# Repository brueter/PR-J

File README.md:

<p align="center">
    <picture>
        <source media="(prefers-color-scheme: dark)" srcset="./images/dark.svg" | width=300>
        <source media="(prefers-color-scheme: light)" srcset="./images/light.svg" | width=300>
        
    </picture>
</p>

## PR and what now?
PR&J is the second name of this project after realizing two things:
- I'd like to be able to put this on a resume.
- Realizing the main features are as follows:
    - Probing
    - Runout detection
    - & Jam detection
> This board also is sandwiched between the hotend and extruder, thus a PR&J.

> If you'd like to know the first name of the board scroll up a bit in the discord

## How does a load cell do all that?
The way this design is set to work is there will be a strain gauge between the extruder and hotend with a set of resistors on it.
When the board experiences even the slightest bit of strain, the value of these resistors changes slightly.
This change is amplified by the tried and true HX717 24 bit amplifier, allowing for over 16 million unique values.
This signal is then read by an on board ATTiny202, and then sent to a klipper MCU via I<sub>2</sub>C.

Though the first idea that comes to mind with load cells is probing (which is still the main feature of this project), the ability to detect this strain can also be used to interpret forces between the hotend and extruder in both positive and negative directions.
We're still workshopping ideas that could come from this one feature, but some we would like to consider are:
- Runout detection
- Jam detection
- Detecting skipped steps
- One-click pressure advance tuning
- One-click max flow rate calculation

Some "theoreticals" that will need extensive testing but may be possible:
- Spaghetti detection
- Crash detection
- Flow rate change compensation

## Sign me up!
Actually I'd love to!
We're in the process of establishing a small beta test group for main boards and two types of strain gauges. The initial testing phase likely won't involve much printing, focusing instead on gathering data to study the behavior of these strain gauges, as well as test consistency.
As we develop more, the strain gauges we currently have may be adapted to some toolheads, so it's likely that new hardware won't even have to be sent for real world testing.
We're also looking for people that may have experience with any of the following for helping with development of the project itself.
- Skilled programmers, especially those familiar with klipper
- Electronics engineers
- CAD experts
If you're interested in contributing, ongoing discussions are hosted on the [Armchair Engineering discord server](https://discord.gg/armchairengineeringsux) in [this specific channel](https://discord.com/channels/1029426383614648421/1141480604844703745).

## What now?
As of the repository's creation, parts are on the way, and the board ordering process is nearly finalized. The initial batch of test boards will comprise approximately 10 main boards and 20 strain gauges (10 of each design).
Regular updates will be posted in the Armchair engineering project thread. Feel free to reach out to me there or through [my discord](https://discord.com/users/96435324275658752) if you have any questions.

Here's what we've got so far :)

<picture>
  <source srcset="./images/boards.png">
  
</picture>

## Helpers
- Electronics
    - [fisheiyy](https://github.com/fisheiyy)
    - [tanaes](https://github.com/tanaes)
    - [calithameridi](http://github.com/calithameridi/)
- Hardware
    - [tanaes](https://github.com/tanaes)
    - [bwnance](https://github.com/bwnance)
- Software
    - [detunedcalliope](https://github.com/detunedcalliope)

## Legal

Shield: [![CC BY-NC-SA 4.0][cc-by-nc-sa-shield]][cc-by-nc-sa]

This work is licensed under a
[Creative Commons Attribution-NonCommercial-ShareAlike 4.0 International License][cc-by-nc-sa].

[![CC BY-NC-SA 4.0][cc-by-nc-sa-image]][cc-by-nc-sa]

[cc-by-nc-sa]: http://creativecommons.org/licenses/by-nc-sa/4.0/
[cc-by-nc-sa-image]: https://licensebuttons.net/l/by-nc-sa/4.0/88x31.png
[cc-by-nc-sa-shield]: https://img.shields.io/badge/License-CC%20BY--NC--SA%204.0-lightgrey.svg

FOR COMMERCIAL RIGHTS CONTACT AT brueter918@gmail.com

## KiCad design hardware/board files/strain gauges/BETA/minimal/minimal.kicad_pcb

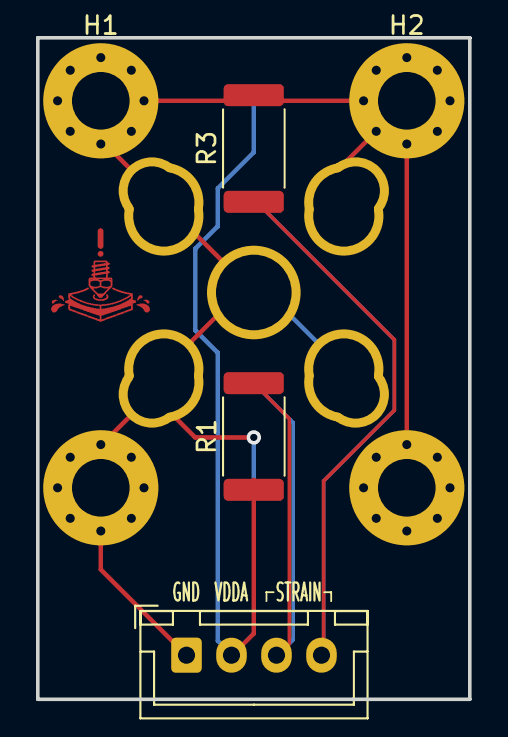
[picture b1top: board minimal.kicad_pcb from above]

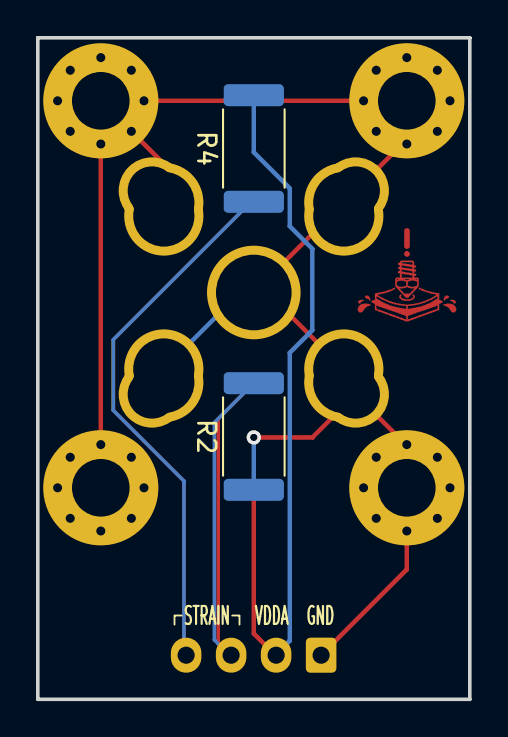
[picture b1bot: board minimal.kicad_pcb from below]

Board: 2 copper layers, 24.0 x 36.8 mm, 10 parts (2 on the bottom side), 4 nets.

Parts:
H1, H2, H3, H4: MountingHole_Pad; MountingHole_3.2mm_M3_Pad_Via
J1: PR&J; JST_XH_B4B-XH-A_1x04_P2.50mm_Vertical
R1, R2, R3, R4: 1k; R_2512_6332Metric
U1: hotend mounting holes

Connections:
GND: H1.1, H2.1, H3.1, H4.1, J1.1, R2.1, R3.2, U1.1 (GND)
IN+: J1.3, R1.2, R2.2
IN-: J1.4, R3.1, R4.1
VDDA: J1.2, R1.1, R4.2

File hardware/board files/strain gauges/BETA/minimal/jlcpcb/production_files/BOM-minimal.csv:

Comment,Designator,Footprint,LCSC
PR&J,J1,PinSocket_1x04_P2.54mm_Vertical,
1k,R3,R_2512_6332Metric,
MountingHole_Pad,H1,MountingHole_3.2mm_M3_Pad_Via,
~,U1,hotend mounting holes,
MountingHole_Pad,H2,MountingHole_3.2mm_M3_Pad_Via,
1k,R1,R_2512_6332Metric,
MountingHole_Pad,H3,MountingHole_3.2mm_M3_Pad_Via,
MountingHole_Pad,H4,MountingHole_3.2mm_M3_Pad_Via,
1k,R2,R_2512_6332Metric,
1k,R4,R_2512_6332Metric,

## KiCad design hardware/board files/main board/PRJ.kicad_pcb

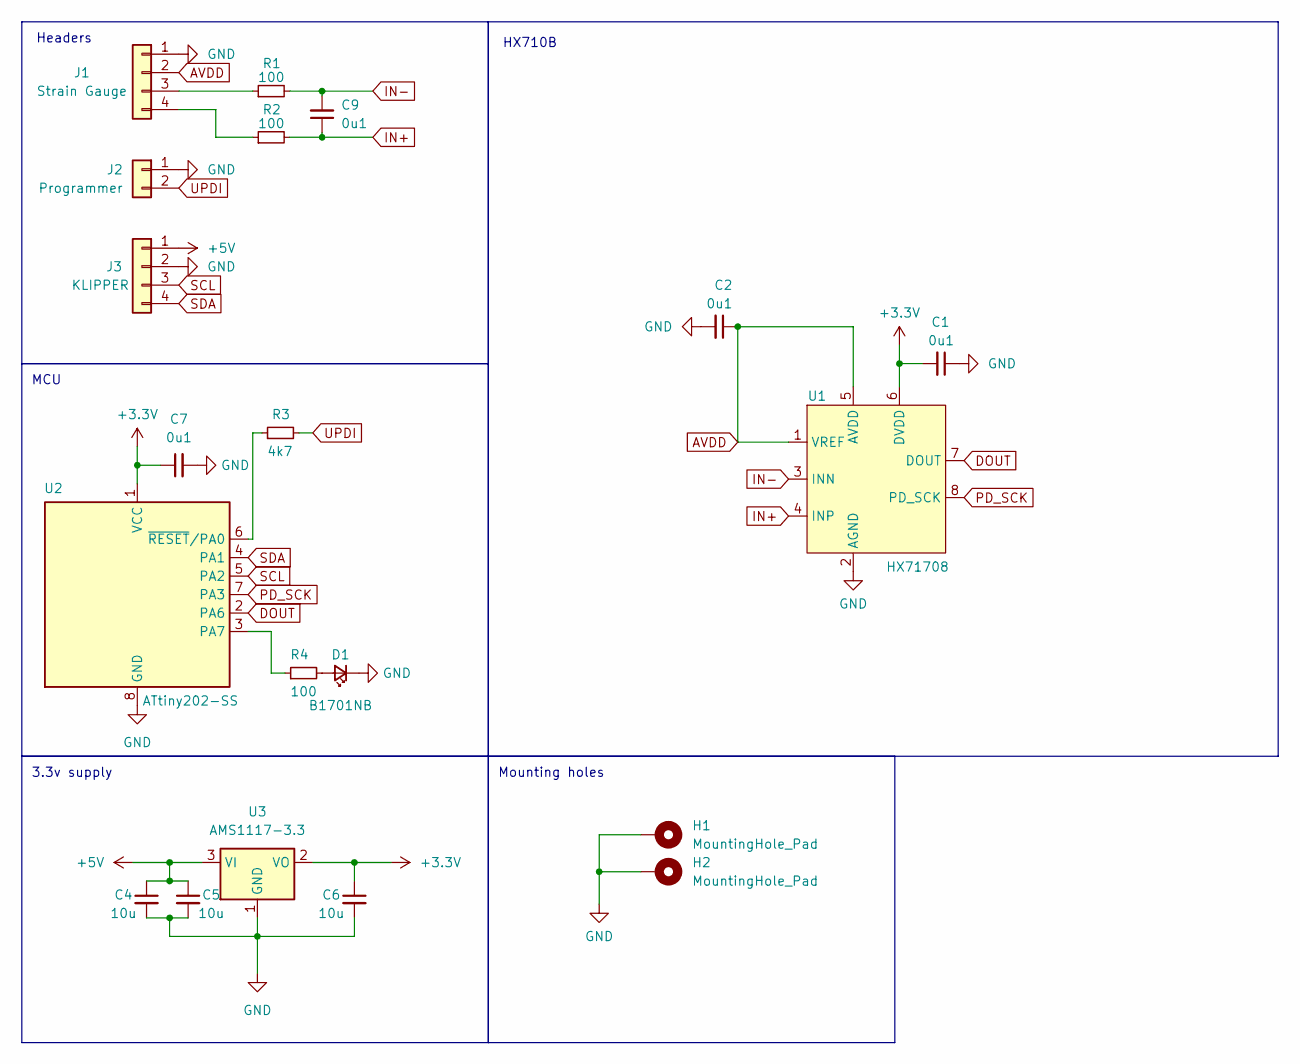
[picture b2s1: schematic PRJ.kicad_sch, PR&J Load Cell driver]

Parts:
C1, C2, C7, C9: 0u1; C_0402_1005Metric
C4, C5, C6: 10u; C_0402_1005Metric
D1: B1701NB; LED_0402_1005Metric
H1, H2: MountingHole_Pad; MountingHole_3.2mm_M3_Pad_Via
J1: Strain Gauge; PinSocket_1x04_P2.54mm_Vertical
J2: Programmer; PinSocket_1x02_P2.54mm_Vertical
J3: KLIPPER; PinSocket_1x04_P2.54mm_Vertical
R1, R2, R4: 100; R_0402_1005Metric
R3: 4k7; R_0402_1005Metric
U1: HX71708; SOIC-8_3.9x4.9mm_P1.27mm
U2: ATtiny202-SS; SOIC-8_3.9x4.9mm_P1.27mm
U3: AMS1117-3.3; SOT-223-3_TabPin2

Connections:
+3.3V: C1.2, C6.1, C7.1, U1.6 (DVDD), U2.1 (VCC), U3.2 (VO)
+5V: C4.1, C5.1, J3.1, U3.3 (VI)
AVDD: C2.1, J1.2, U1.1 (VREF), U1.5 (AVDD)
DOUT: U1.7 (DOUT), U2.2 (PA6)
GND: C1.1, C2.2, C4.2, C5.2, C6.2, C7.2, D1.1 (K), H1.1, H2.1, J1.1, J2.1, J3.2, U1.2 (AGND), U2.8 (GND), U3.1 (GND)
IN+: C9.1, R2.2, U1.4 (INP)
IN-: C9.2, R1.2, U1.3 (INN)
unnamed: D1.2 (A), R4.2
unnamed: J1.3, R1.1
unnamed: J1.4, R2.1
unnamed: R4.1, U2.3 (PA7)
unnamed: R3.1, U2.6 (~RESET/PA0)
PD_SCK: U1.8 (PD_SCK), U2.7 (PA3)
SCL: J3.3, U2.5 (PA2)
SDA: J3.4, U2.4 (PA1)
UPDI: J2.2, R3.2

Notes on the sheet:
Headers
HX710B
Mounting holes
3.3v supply
MCU

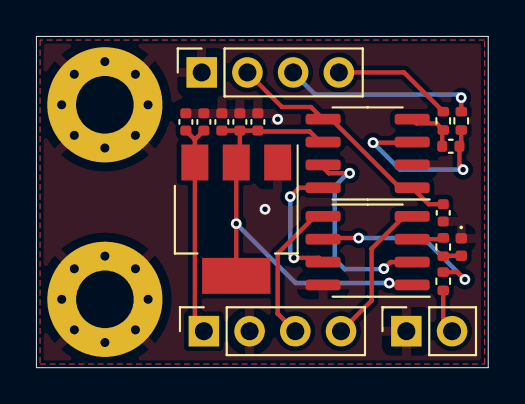
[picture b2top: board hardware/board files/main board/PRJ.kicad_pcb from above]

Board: 2 copper layers, 25.1 x 18.4 mm, 20 parts (0 on the bottom side), 16 nets.

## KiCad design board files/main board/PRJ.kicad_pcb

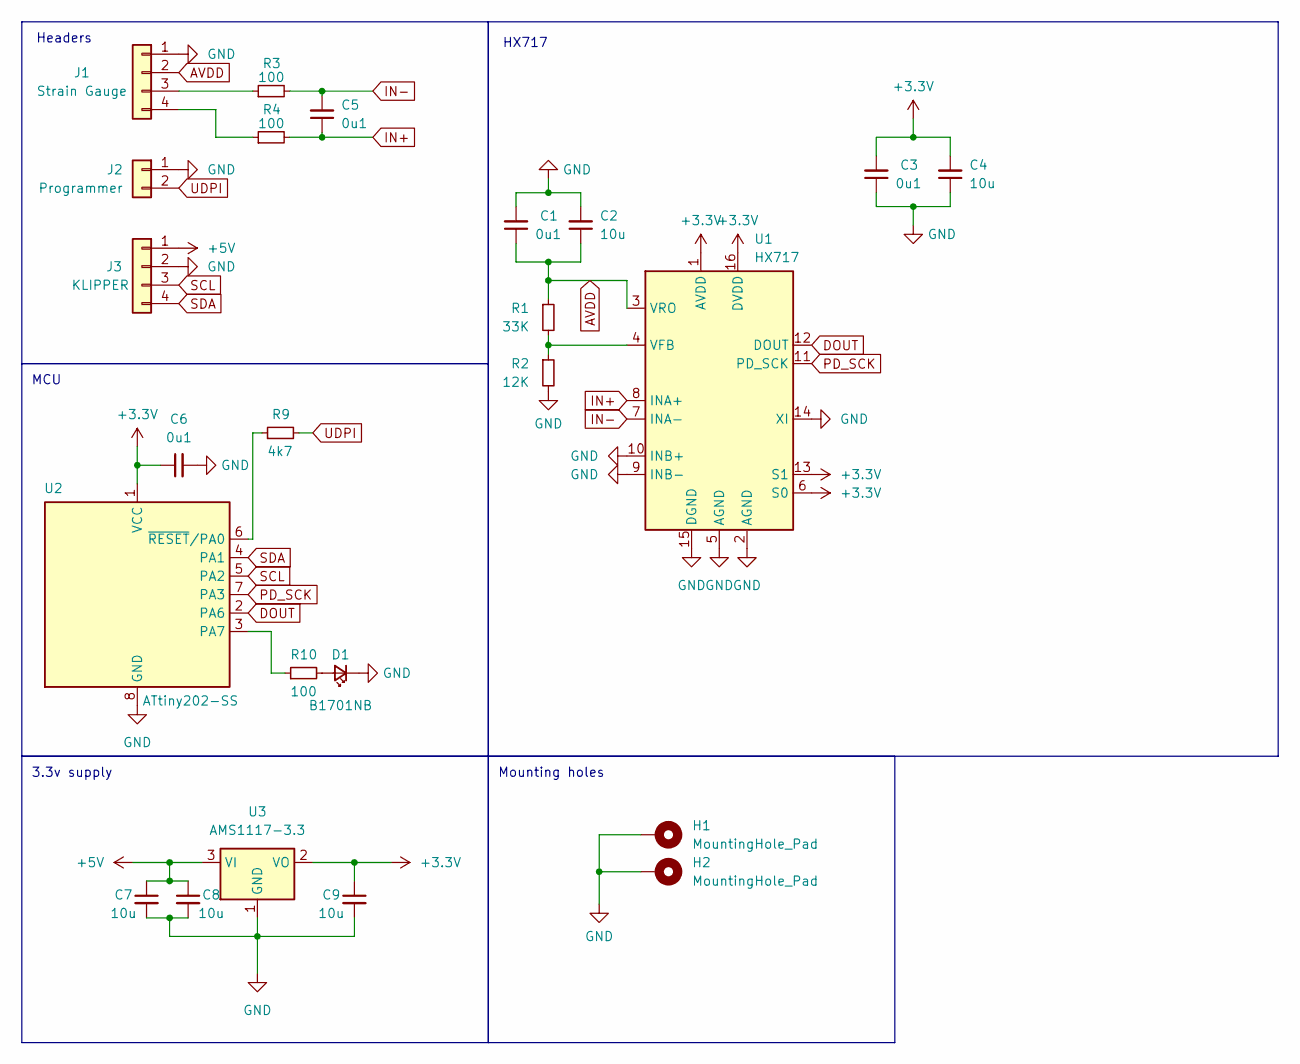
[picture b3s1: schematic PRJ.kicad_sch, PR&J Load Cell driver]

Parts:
C1, C3, C5, C6: 0u1; C_0805_2012Metric_Pad1.18x1.45mm_HandSolder
C2, C4, C7, C8, C9: 10u; C_0805_2012Metric_Pad1.18x1.45mm_HandSolder
D1: B1701NB; LED_0805_2012Metric_Pad1.15x1.40mm_HandSolder
H1, H2: MountingHole_Pad; MountingHole_3.2mm_M3_Pad_Via
J1: Strain Gauge; PinSocket_1x04_P2.54mm_Vertical
J2: Programmer; PinSocket_1x02_P2.54mm_Vertical
J3: KLIPPER; PinSocket_1x04_P2.54mm_Vertical
R1: 33K; R_0805_2012Metric_Pad1.20x1.40mm_HandSolder
R2: 12K; R_0805_2012Metric_Pad1.20x1.40mm_HandSolder
R3, R4, R10: 100; R_0805_2012Metric_Pad1.20x1.40mm_HandSolder
R9: 4k7; R_0805_2012Metric_Pad1.20x1.40mm_HandSolder
U1: HX717; SOP-16_3.9x9.9mm_P1.27mm
U2: ATtiny202-SS; SOIC-8_3.9x4.9mm_P1.27mm
U3: AMS1117-3.3; SOT-223-3_TabPin2

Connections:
+3.3V: C3.2, C4.2, C6.1, C9.1, U1.1 (AVDD), U1.6 (S0), U1.13 (S1), U1.16 (DVDD), U2.1 (VCC), U3.2 (VO)
+5V: C7.1, C8.1, J3.1, U3.3 (VI)
AVDD: C1.1, C2.1, J1.2, R1.1, U1.3 (VRO)
DOUT: U1.12 (DOUT), U2.2 (PA6)
GND: C1.2, C2.2, C3.1, C4.1, C6.2, C7.2, C8.2, C9.2, D1.1 (K), H1.1, H2.1, J1.1, J2.1, J3.2, R2.2, U1.2 (AGND), U1.5 (AGND), U1.9 (INB-), U1.10 (INB+), U1.14 (XI), U1.15 (DGND), U2.8 (GND), U3.1 (GND)
IN+: C5.1, R4.2, U1.8 (INA+)
IN-: C5.2, R3.2, U1.7 (INA-)
unnamed: D1.2 (A), R10.2
unnamed: J1.3, R3.1
unnamed: J1.4, R4.1
unnamed: R1.2, R2.1, U1.4 (VFB)
unnamed: R10.1, U2.3 (PA7)
unnamed: R9.1, U2.6 (~RESET/PA0)
PD_SCK: U1.11 (PD_SCK), U2.7 (PA3)
SCL: J3.3, U2.5 (PA2)
SDA: J3.4, U2.4 (PA1)
UDPI: J2.2, R9.2

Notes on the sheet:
Headers
HX717
Mounting holes
3.3v supply
MCU

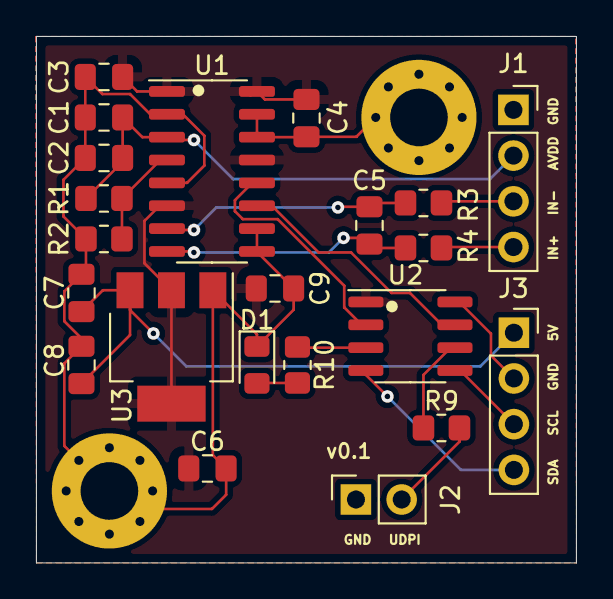
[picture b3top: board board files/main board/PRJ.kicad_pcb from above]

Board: 4 copper layers, 30.0 x 29.2 mm, 24 parts (0 on the bottom side), 17 nets.

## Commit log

2023-08-27 initial commit, contains board files
2023-08-27 added readme
2023-08-27 added banner
2023-08-27 changed images
2023-08-27 fixed images
2023-08-27 added light/dark theming
2023-08-27 converted images to svg
2023-08-27 pictures arent massive anymore
2023-08-27 added links to credits
2023-08-27 fixed strain gauge routing, added images of all boards
2023-08-27 moved images of boards
2023-08-27 added PRJ logo to strain gauge boards
2023-08-27 updated credits
2023-08-27 updates credits
2023-08-27 changed punctuation on readme
2023-08-27 more readme changes
2023-08-28 mistake in readme
2023-08-28 Added software license
2023-08-28 Update LICENSE
2023-08-29 first revision of on board firmware, separate hardware and software folders
2023-08-29 added software license, updated credits
2023-08-29 fixed license and readme
2023-08-29 fixed license
2023-09-04 overhauled main board, updated credits
2023-09-04 adjusted mainboard
2023-09-05 finalized boards for production
2023-09-05 Create LICENSE
2023-09-08 added initial prototype of production unit with attiny202 and hx71708
2023-10-08 updated 202 firmware to add software low pass filtering and median filtering
2023-10-09 added cad and stl files for initial test version of a modified stealthburner, currently being reffered to as stealthjelly
2023-10-09 fixed issue with front part
2023-10-09 fixed heat sets being too small on front
2023-10-11 added software to analyze data from an excel spreadsheet alongside various filtering methods
